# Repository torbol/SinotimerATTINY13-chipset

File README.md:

# Introducción

Por necesidad y urgencia se decidió adquirir por Aliexpress un protector de sobretensiones transitorias SINOTIMER. Al ver que no se mencionaba ni en la ficha del producto ni en las instrucciones nada referente a si tiene memoria para guardar los ajustes que se establezcan, me decidí a crear un pequeño chip para que en caso de que se fuera la luz por completo, el aparato se reajustara automáticamente.

## Funcionamiento (Idea)

Se supuso ante el peor de los casos que el aparato no contaría con memoria interna, por lo que partí de que la propia alimentación continuada del dispositivo haría que mantuviese los ajustes (253V como máximo de sobretensión, un 10% por encima de la tensión nominal según reglamento de baja tensión, es decir, un 10% de 230V para España). 

Lo que se propone en este proyecto es crear un pequeño chip que se conecte como un pequeño vampiro a los botones del aparato SET y DOWN (ya que queremos bajar la que viene por defecto de 280V a 253V). Para ello se idea el siguiente circuito:

<div align="center">
	
</div>

Como podemos ver cuenta con 3 pines en la zona superior y dos en la inferior, las dos inferiores deberán ir al GND y a la salida de un regulador de voltaje del SINOTIMER que proporcione alimentación de 5V, por ejemplo uno que lo proporciona es el que alimenta el microcontrolador interno del aparato para comprobar las diferencias de tensión y activar relés. El chip aquí presentado es sencillo, consiste en dos optoacopladores que se activarán según una secuencia indicada por nuestro microcontrolador ATTINY13. Esta secuencia solo se ejecutará una única vez al alimentar el aparato (SINOTIMER), luego se bajará la alimentación para que el chip quede en un estado de consumo mínimo.
## Conexiones chip:
<div align="middle">
  
</div>

### Esquemático circuito:
<div align="center">
   
</div>

# Resultado
## Video

https://github.com/user-attachments/assets/8c8c64fe-9294-41ef-b0de-fd418badb5d0

## Resultado final una vez fabricada la pcb
Aunque es una versión anterior sin el tercer pin de arriba (común botones), funciona exactamente igual (va a común del aparato, que debe ser el mismo para todos, solo que al estar el chip aislado por los optoacpoladores, se optó por el nuevo diseño para tener el mínimo impacto en la pcb del microcontrolador del SINOTIMER, de esta manera, es como si pulsásemos los botones nosotros mismos.

https://github.com/user-attachments/assets/2a9f2775-4988-4b48-812e-7c7adac6edf6

# Moraleja de toda esta historia
Finalmente tras haber desarrollado este pequeño sistema, no fue necesario implementarlo, pues el SINOTIMER que recibí sí que cuenta con memoria en caso de que se quede totalmente sin alimentación. Aún así he decidido subir este proyecto pues podría ser muy útil para otros aparatos, por ejemplo un temporizador para una lavadora antigua, juguetes infantiles que cuenten con botonera, como pequeño interruptor para circuitos de mayor voltaje (ya que los extremos de los octoacopladores están totalmente aislados del ATTINY13). En el caso del modelo P817 utilizado para este chip, soporta hasta 35V colector-emisor o 6V emisor-colector (y el aislamiento que aguantan entre Anodo/Catodo - Emisor/Colector es de 5000V por lo que no se estropearía el chip, solo los optoacopladores):

<div align="center">
   
</div>

## Extra: Para mí lo más importante
Para el modo "deep sleep" no encontré mucha información en internet y lo poco que encontraba no me gustaba. Finalmente a partir del datasheet, adapté mi propio código para el ATTINY13A, para más información visita el proyecto [MRE-ATTINY13A-DEEP_SLEEP](https://github.com/torbol/MRE-ATTINY13A-DEEP_SLEEP).

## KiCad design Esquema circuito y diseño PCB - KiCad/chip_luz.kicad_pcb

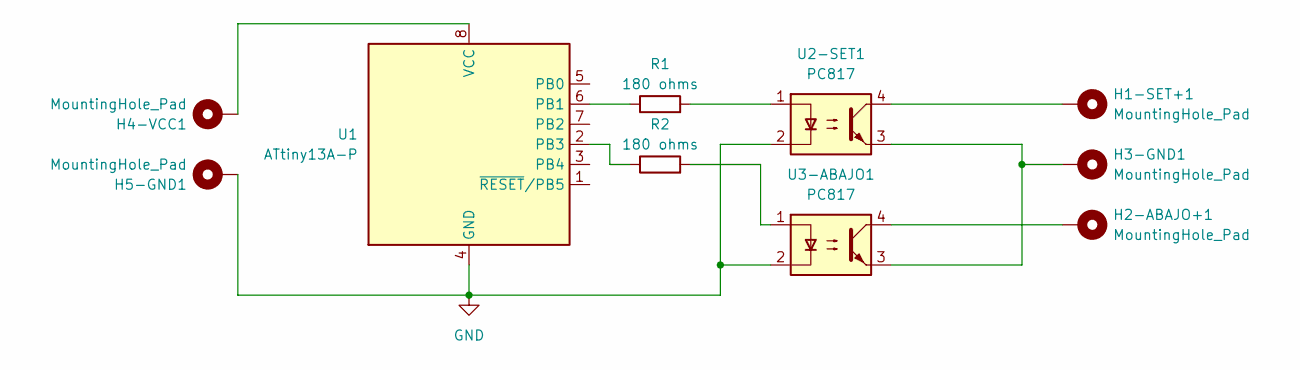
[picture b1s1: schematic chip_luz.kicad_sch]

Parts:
H1-SET+1, H2-ABAJO+1, H3-GND1, H4-VCC1, H5-GND1: MountingHole_Pad; MountingHole_2.2mm_M2_DIN965_Pad
R1, R2: 180 ohms; R_Axial_DIN0411_L9.9mm_D3.6mm_P12.70mm_Horizontal
U1: ATtiny13A-P; DIP-8_W7.62mm_Socket_LongPads
U2-SET1, U3-ABAJO1: PC817; DIP-4_W7.62mm

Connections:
GND: H5-GND1.1, U1.4 (GND), U2-SET1.2, U3-ABAJO1.2
unnamed: H1-SET+1.1, U2-SET1.4
unnamed: H2-ABAJO+1.1, U3-ABAJO1.4
unnamed: H3-GND1.1, U2-SET1.3, U3-ABAJO1.3
unnamed: R1.2, U2-SET1.1
unnamed: R2.2, U3-ABAJO1.1
unnamed: R1.1, U1.6 (PB1)
unnamed: R2.1, U1.2 (PB3)
unnamed: H4-VCC1.1, U1.8 (VCC)

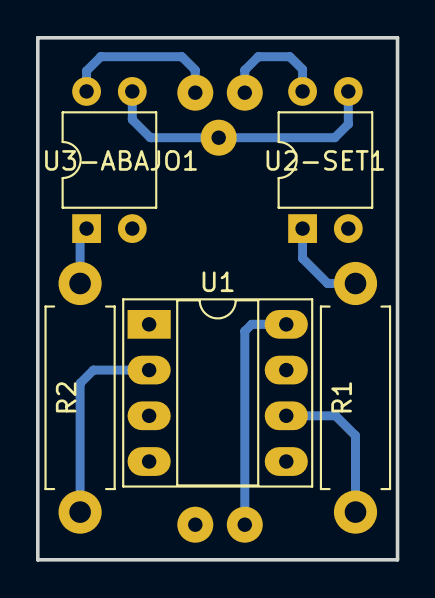
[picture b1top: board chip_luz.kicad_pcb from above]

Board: 2 copper layers, 20.0 x 29.0 mm, 10 parts (0 on the bottom side), 9 nets.

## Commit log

2024-09-09 Se sube proyecto finalizado y Readme a medias
2024-09-09 Update README.md
    Añadida documentación y videos
2024-09-09 Update README.md
    Añadida información a README.md
2024-09-10 Update README.md
    Añadida documentación a README.md
2024-09-10 Actualizar README.md
    Corrección Readme.md
2024-09-11 Update README.md
    Pequeña corrección video resultado
